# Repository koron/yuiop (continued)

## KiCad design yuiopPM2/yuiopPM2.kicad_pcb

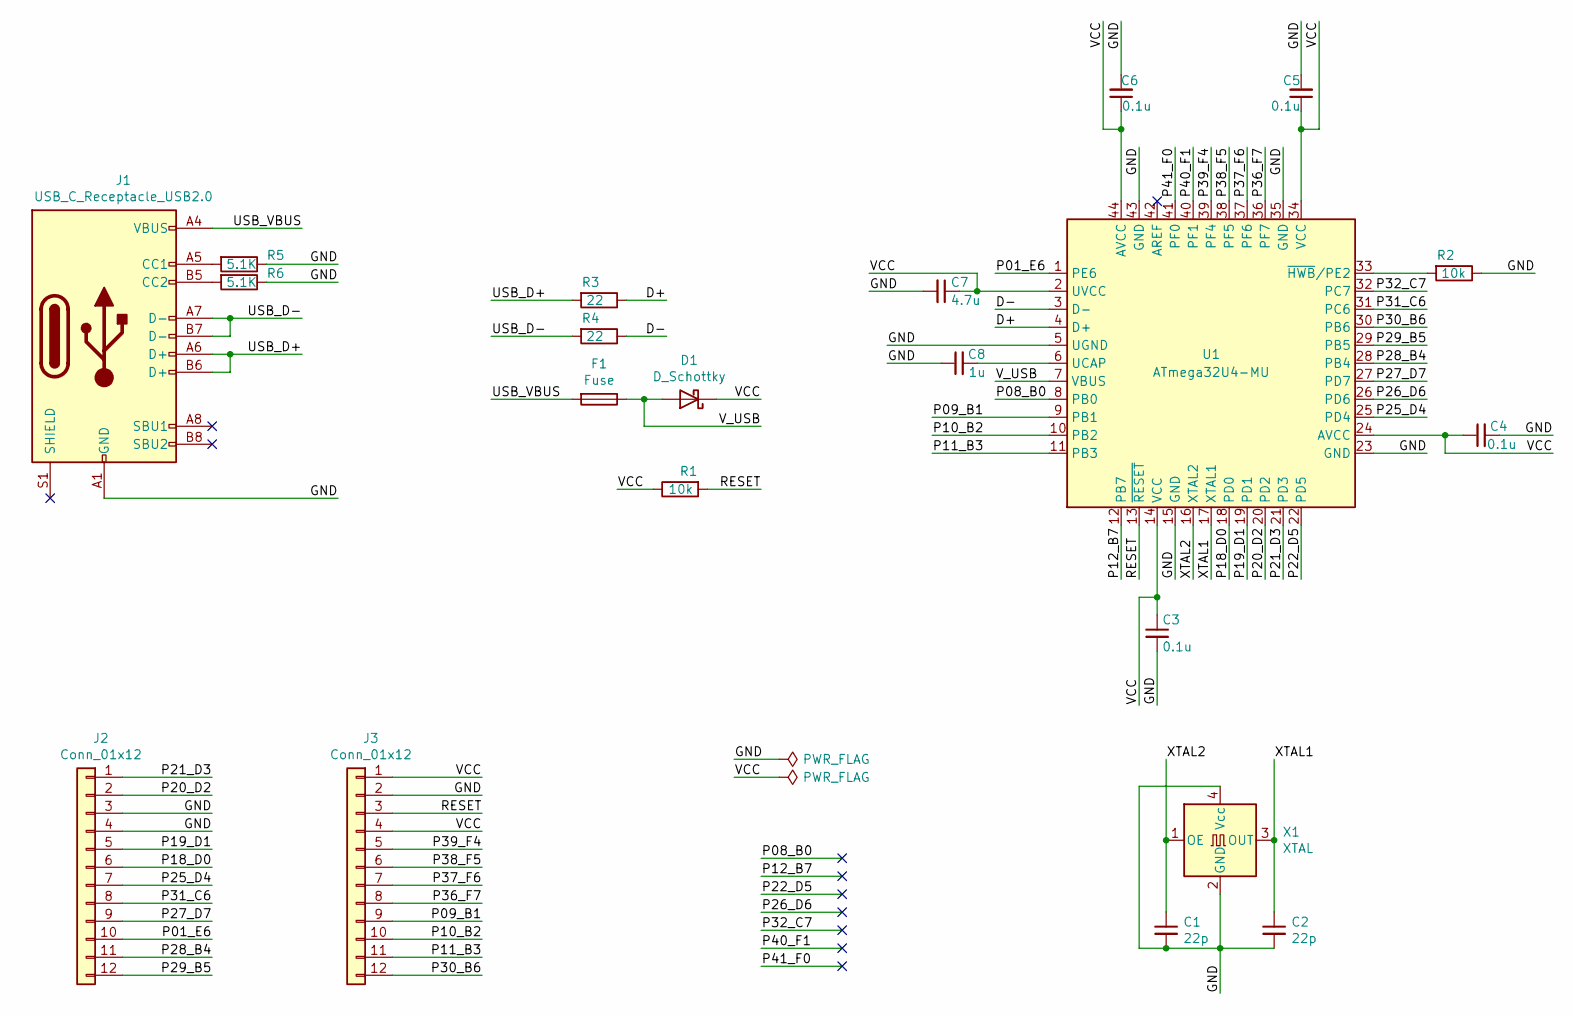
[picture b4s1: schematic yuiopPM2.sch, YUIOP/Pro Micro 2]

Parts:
C1, C2: 22p; C_0603_1608Metric
C3, C4, C5, C6: 0.1u; C_0603_1608Metric
C7: 4.7u; C_0603_1608Metric
C8: 1u; C_0603_1608Metric
D1: D_Schottky; D_SOD-123
F1: Fuse; Fuse_1206_3216Metric
J1: USB_C_Receptacle_USB2.0; USB_C_Receptacle_XKB_U262-16XN-4BVC11
J2, J3: Conn_01x12; SpringPinHeader-01x12
R1, R2: 10k; R_0603_1608Metric
R3, R4: 22; R_0603_1608Metric
R5, R6: 5.1K; R_0603_1608Metric
U1: ATmega32U4-MU; TQFP-44_10x10mm_P0.8mm
X1: XTAL; Oscillator_SMD_SeikoEpson_SG8002CE-4Pin_3.2x2.5mm

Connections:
/D+: R3.1, U1.4 (D+)
/D-: R4.1, U1.3 (D-)
/GND: C1.2, C2.2, C3.2, C4.2, C5.2, C6.2, C7.2, C8.1, J1.A1 (GND), J1.A12 (GND), J1.B1 (GND), J1.B12 (GND), J2.3, J2.4, J3.2, R2.1, R5.1, R6.1, U1.5 (UGND), U1.15 (GND), U1.23 (GND), U1.35 (GND), U1.43 (GND), X1.2 (GND), X1.4 (Vcc)
/P01_E6: J2.10, U1.1 (PE6)
/P08_B0: U1.8 (PB0)
/P09_B1: J3.9, U1.9 (PB1)
/P10_B2: J3.10, U1.10 (PB2)
/P11_B3: J3.11, U1.11 (PB3)
/P12_B7: U1.12 (PB7)
/P18_D0: J2.6, U1.18 (PD0)
/P19_D1: J2.5, U1.19 (PD1)
/P20_D2: J2.2, U1.20 (PD2)
/P21_D3: J2.1, U1.21 (PD3)
/P22_D5: U1.22 (PD5)
/P25_D4: J2.7, U1.25 (PD4)
/P26_D6: U1.26 (PD6)
/P27_D7: J2.9, U1.27 (PD7)
/P28_B4: J2.11, U1.28 (PB4)
/P29_B5: J2.12, U1.29 (PB5)
/P30_B6: J3.12, U1.30 (PB6)
/P31_C6: J2.8, U1.31 (PC6)
/P32_C7: U1.32 (PC7)
/P36_F7: J3.8, U1.36 (PF7)
/P37_F6: J3.7, U1.37 (PF6)
/P38_F5: J3.6, U1.38 (PF5)
/P39_F4: J3.5, U1.39 (PF4)
/P40_F1: U1.40 (PF1)
/P41_F0: U1.41 (PF0)
/RESET: J3.3, R1.2, U1.13 (~RESET)
/USB_D+: J1.A6 (D+), J1.B6 (D+), R3.2
/USB_D-: J1.A7 (D-), J1.B7 (D-), R4.2
/USB_VBUS: F1.2, J1.A4 (VBUS), J1.A9 (VBUS), J1.B4 (VBUS), J1.B9 (VBUS)
/VCC: C3.1, C4.1, C5.1, C6.1, C7.1, D1.1 (K), J3.1, J3.4, R1.1, U1.2 (UVCC), U1.14 (VCC), U1.24 (AVCC), U1.34 (VCC), U1.44 (AVCC)
/V_USB: D1.2 (A), F1.1, U1.7 (VBUS)
/XTAL1: C2.1, U1.17 (XTAL1), X1.3 (OUT)
/XTAL2: C1.1, U1.16 (XTAL2), X1.1 (OE)
unnamed: C8.2, U1.6 (UCAP)
unnamed: J1.A5 (CC1), R5.2
unnamed: J1.B5 (CC2), R6.2
unnamed: R2.2, U1.33 (~HWB~/PE2)

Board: 2 copper layers, 21 parts (0 on the bottom side), 33 nets, no tracks yet.

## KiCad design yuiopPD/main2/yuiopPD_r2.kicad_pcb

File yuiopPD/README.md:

# YUIOP/PD

"PD" means "Pointing Device".  A track ball and 6 buttons pointing device
project.

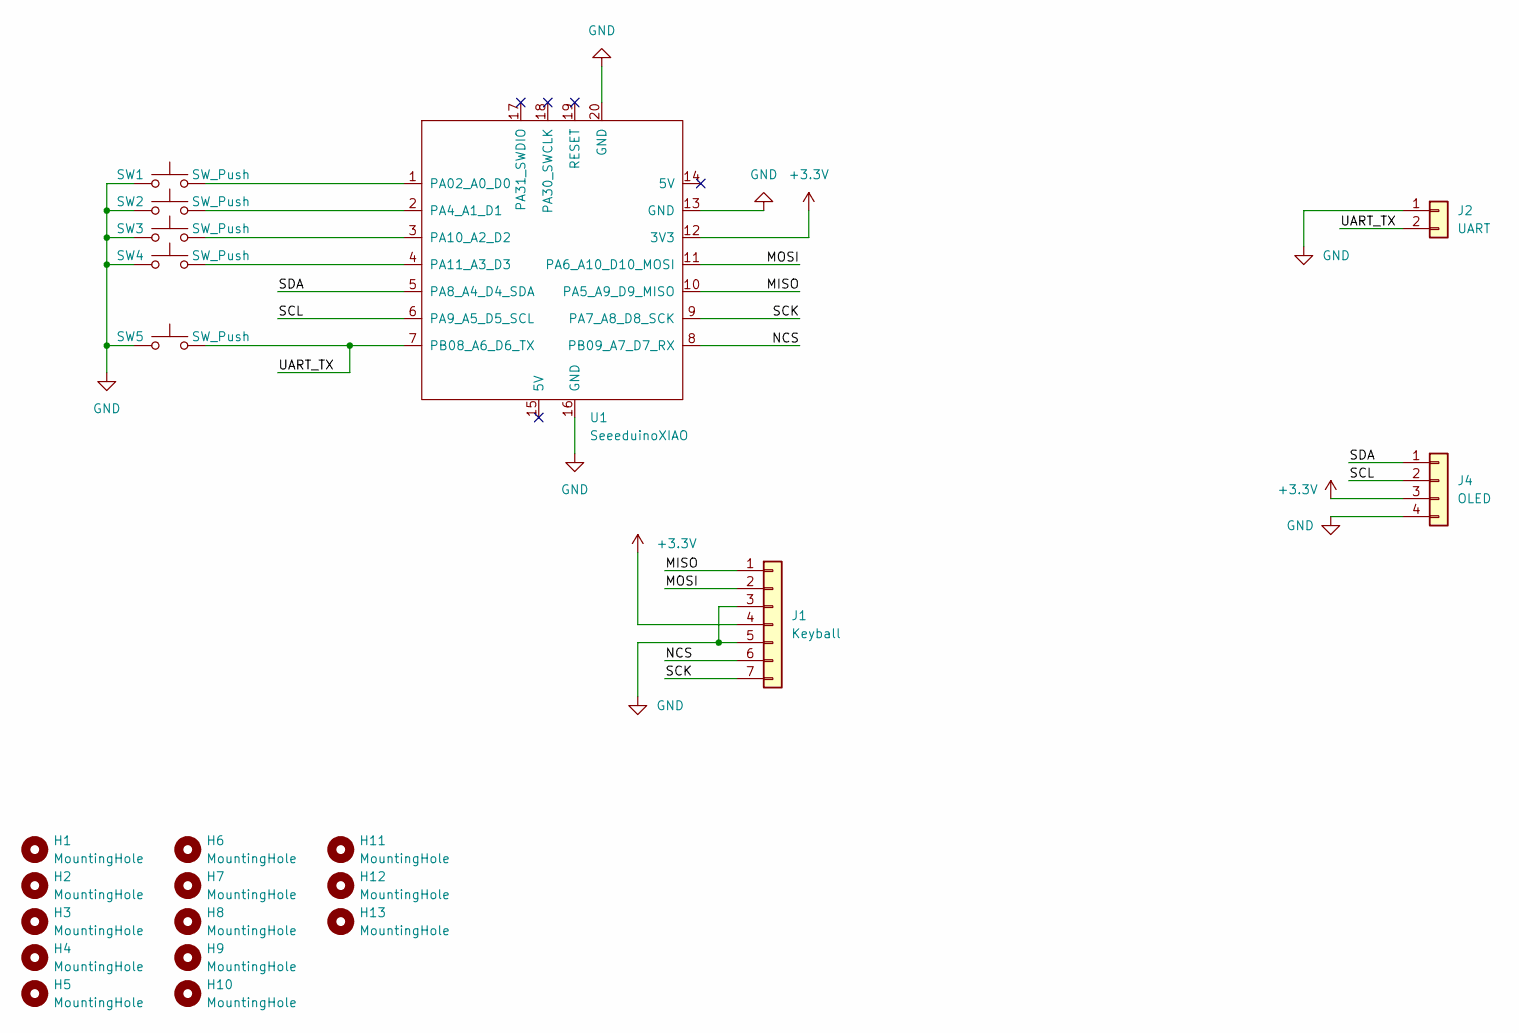
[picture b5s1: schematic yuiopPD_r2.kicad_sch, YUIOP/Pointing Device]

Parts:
H1, H2, H3, H4, H5, H6, H7, H8, H9, H10, H11, H12, H13: MountingHole; MountingHole_2.1mm
J1: Keyball; KeyballSensor_on_PCB
J2: UART; PinHeader_1x02_P2.54mm_Vertical
J4: OLED; OLED_128x32
SW1, SW2, SW3, SW4, SW5: SW_Push; SW_PUSH-12mm_v2
U1: SeeeduinoXIAO; Seeeduino XIAO TH r2

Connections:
+3V3: J1.4, J4.3, U1.12 (3V3)
/MISO: J1.1, U1.10 (PA5_A9_D9_MISO)
/MOSI: J1.2, U1.11 (PA6_A10_D10_MOSI)
/NCS: J1.6, U1.8 (PB09_A7_D7_RX)
/SCK: J1.7, U1.9 (PA7_A8_D8_SCK)
/SCL: J4.2, U1.6 (PA9_A5_D5_SCL)
/SDA: J4.1, U1.5 (PA8_A4_D4_SDA)
/UART_TX: J2.2, SW5.2, U1.7 (PB08_A6_D6_TX)
GND: J1.3, J1.5, J2.1, J4.4, SW1.1, SW2.1, SW3.1, SW4.1, SW5.1, U1.13 (GND), U1.16 (GND), U1.20 (GND)
unnamed: SW1.2, U1.1 (PA02_A0_D0)
unnamed: SW2.2, U1.2 (PA4_A1_D1)
unnamed: SW3.2, U1.3 (PA10_A2_D2)
unnamed: SW4.2, U1.4 (PA11_A3_D3)

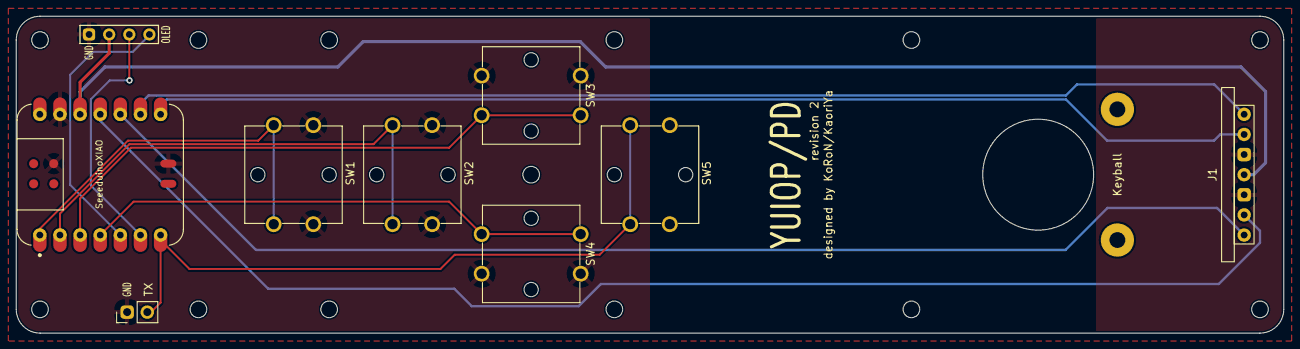
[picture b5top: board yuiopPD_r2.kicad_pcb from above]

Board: 2 copper layers, 160.0 x 40.0 mm, 22 parts (0 on the bottom side), 13 nets.

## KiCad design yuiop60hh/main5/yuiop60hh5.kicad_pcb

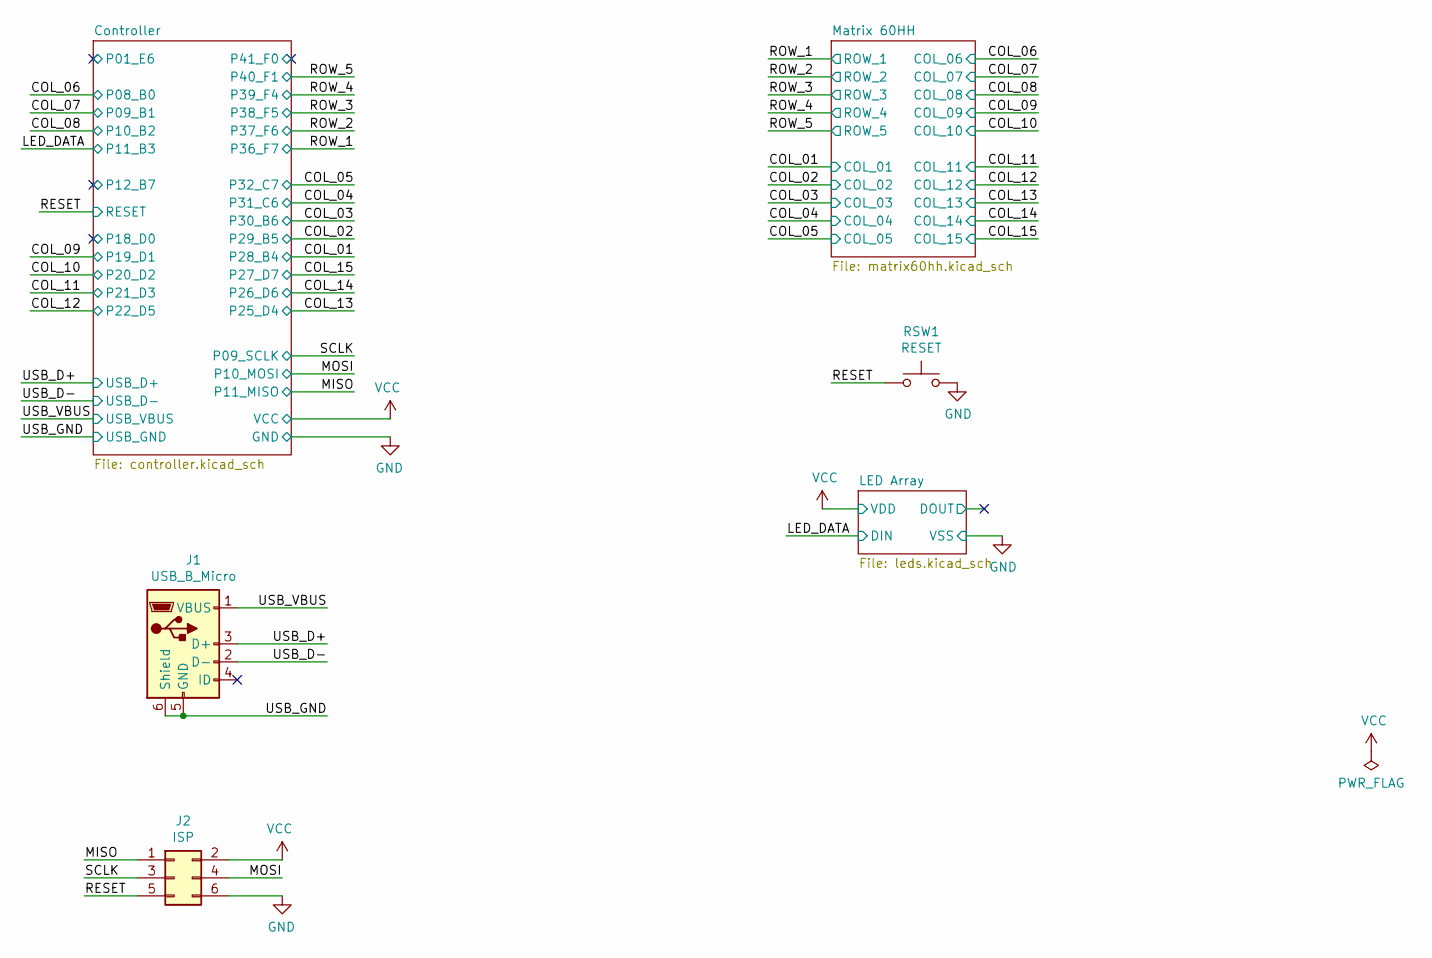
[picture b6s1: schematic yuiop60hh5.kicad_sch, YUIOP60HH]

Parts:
J1: USB_B_Micro; USB_Micro-B_Amphenol_10103594-0001LF_Horizontal
J2: ISP; PinHeader_2x03_P2.54mm_Vertical
RSW1: RESET; SW_Push_1P1T_NO_6x6mm_H9.5mm

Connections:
/COL_07: J2.3; also elsewhere on the board
/COL_08: J2.4; also elsewhere on the board
/LED_DATA: J2.1; also elsewhere on the board
/RESET: J2.5, RSW1.1; also elsewhere on the board
/USB_D+: J1.3 (D+); also elsewhere on the board
/USB_D-: J1.2 (D-); also elsewhere on the board
/USB_VBUS: J1.1 (VBUS); also elsewhere on the board
GND: J1.5 (GND), J1.6 (Shield), J2.6, RSW1.2; also elsewhere on the board
VCC: J2.2; also elsewhere on the board

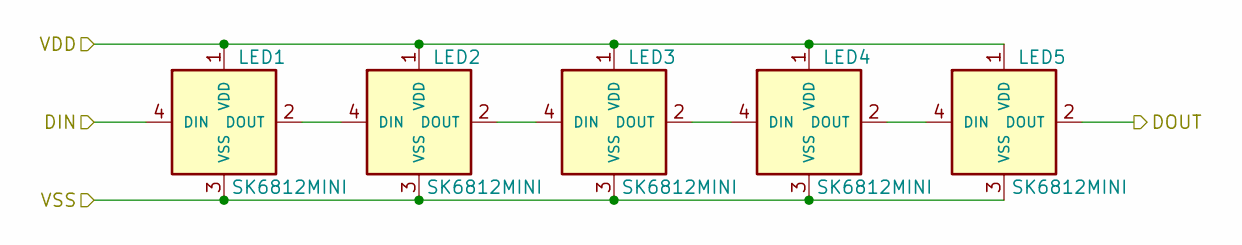
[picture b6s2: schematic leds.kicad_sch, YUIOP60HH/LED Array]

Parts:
LED1, LED2, LED3, LED4, LED5: SK6812MINI; SK6812MINI-E_B

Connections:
/LED Array/DOUT: LED5.2 (DOUT)
/LED_DATA: LED1.4 (DIN); also elsewhere on the board
GND: LED1.3 (VSS), LED2.3 (VSS), LED3.3 (VSS), LED4.3 (VSS), LED5.3 (VSS); also elsewhere on the board
unnamed: LED1.2 (DOUT), LED2.4 (DIN)
unnamed: LED2.2 (DOUT), LED3.4 (DIN)
unnamed: LED3.2 (DOUT), LED4.4 (DIN)
unnamed: LED4.2 (DOUT), LED5.4 (DIN)
VCC: LED1.1 (VDD), LED2.1 (VDD), LED3.1 (VDD), LED4.1 (VDD), LED5.1 (VDD); also elsewhere on the board

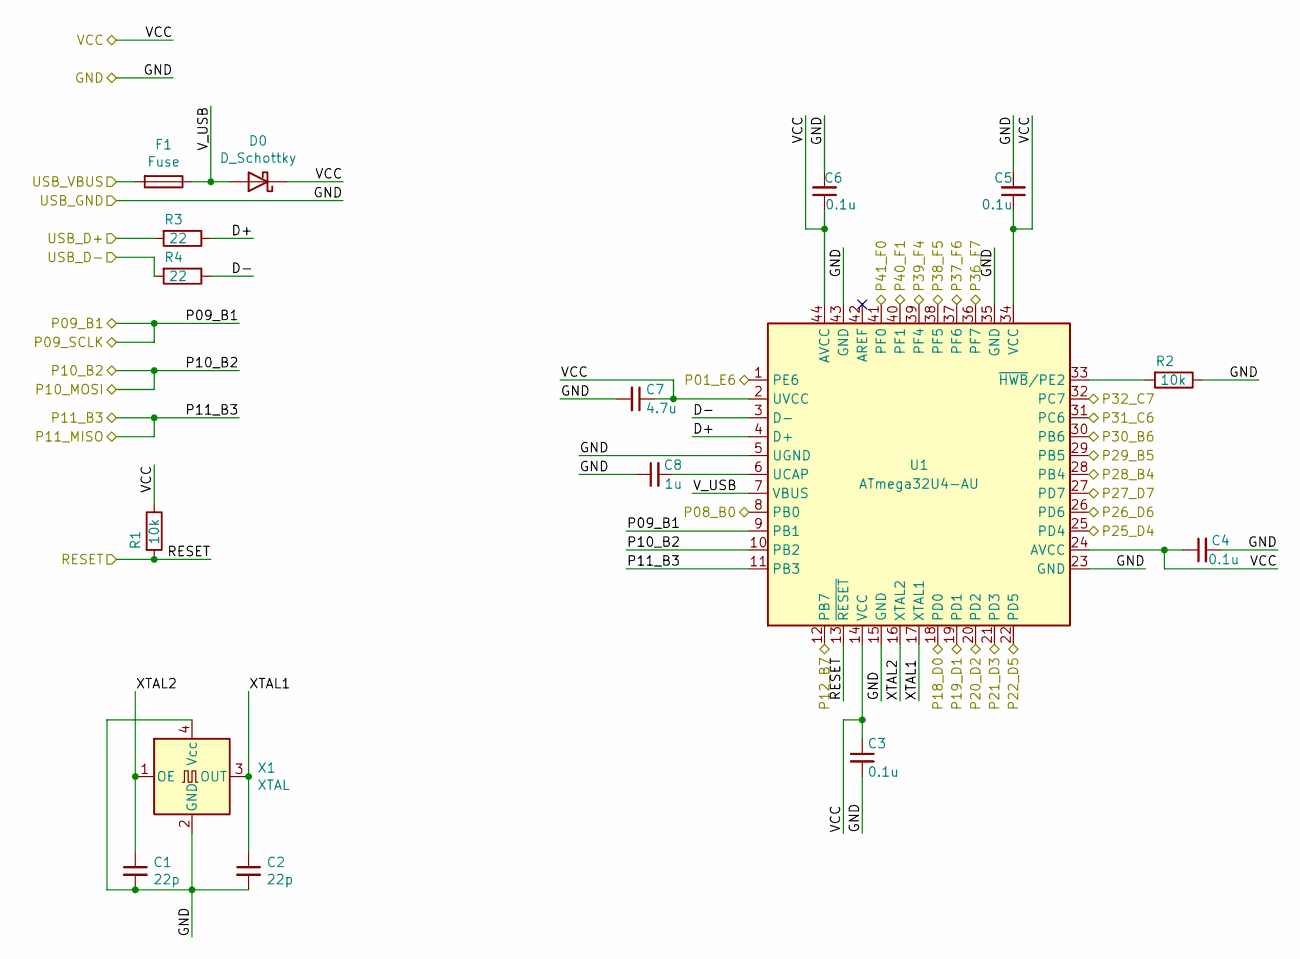
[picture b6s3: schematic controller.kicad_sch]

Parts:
C1, C2: 22p; C_0603_1608Metric_Pad1.08x0.95mm_HandSolder
C3, C4, C5, C6: 0.1u; C_0603_1608Metric_Pad1.08x0.95mm_HandSolder
C7: 4.7u; C_0603_1608Metric_Pad1.08x0.95mm_HandSolder
C8: 1u; C_0603_1608Metric_Pad1.08x0.95mm_HandSolder
D0: D_Schottky; D_SOD-123
F1: Fuse; Fuse_1206_3216Metric_Pad1.42x1.75mm_HandSolder
R1, R2: 10k; R_0603_1608Metric_Pad0.98x0.95mm_HandSolder
R3, R4: 22; R_0603_1608Metric_Pad0.98x0.95mm_HandSolder
U1: ATmega32U4-AU; TQFP-44_10x10mm_P0.8mm
X1: XTAL; Oscillator_SMD_SeikoEpson_SG8002CE-4Pin_3.2x2.5mm

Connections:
/COL_01: U1.28 (PB4); also elsewhere on the board
/COL_02: U1.29 (PB5); also elsewhere on the board
/COL_03: U1.30 (PB6); also elsewhere on the board
/COL_04: U1.31 (PC6); also elsewhere on the board
/COL_05: U1.32 (PC7); also elsewhere on the board
/COL_06: U1.8 (PB0); also elsewhere on the board
/COL_07: U1.9 (PB1); also elsewhere on the board
/COL_08: U1.10 (PB2); also elsewhere on the board
/COL_09: U1.19 (PD1); also elsewhere on the board
/COL_10: U1.20 (PD2); also elsewhere on the board
/COL_11: U1.21 (PD3); also elsewhere on the board
/COL_12: U1.22 (PD5); also elsewhere on the board
/COL_13: U1.25 (PD4); also elsewhere on the board
/COL_14: U1.26 (PD6); also elsewhere on the board
/COL_15: U1.27 (PD7); also elsewhere on the board
/Controller/D+: R3.1, U1.4 (D+)
/Controller/D-: R4.1, U1.3 (D-)
/Controller/P01_E6: U1.1 (PE6)
/Controller/P12_B7: U1.12 (PB7)
/Controller/P18_D0: U1.18 (PD0)
/Controller/P41_F0: U1.41 (PF0)
/Controller/V_USB: D0.2 (A), F1.1, U1.7 (VBUS)
/Controller/XTAL1: C2.1, U1.17 (XTAL1), X1.3 (OUT)
/Controller/XTAL2: C1.1, U1.16 (XTAL2), X1.1 (OE)
/LED_DATA: U1.11 (PB3); also elsewhere on the board
/RESET: R1.2, U1.13 (~RESET); also elsewhere on the board
/ROW_1: U1.36 (PF7); also elsewhere on the board
/ROW_2: U1.37 (PF6); also elsewhere on the board
/ROW_3: U1.38 (PF5); also elsewhere on the board
/ROW_4: U1.39 (PF4); also elsewhere on the board
/ROW_5: U1.40 (PF1); also elsewhere on the board
/USB_D+: R3.2; also elsewhere on the board
/USB_D-: R4.2; also elsewhere on the board
/USB_VBUS: F1.2; also elsewhere on the board
GND: C1.2, C2.2, C3.2, C4.2, C5.2, C6.2, C7.2, C8.1, R2.1, U1.5 (UGND), U1.15 (GND), U1.23 (GND), U1.35 (GND), U1.43 (GND), X1.2 (GND), X1.4 (Vcc); also elsewhere on the board
unnamed: C8.2, U1.6 (UCAP)
unnamed: R2.2, U1.33 (~HWB/PE2)
VCC: C3.1, C4.1, C5.1, C6.1, C7.1, D0.1 (K), R1.1, U1.2 (UVCC), U1.14 (VCC), U1.24 (AVCC), U1.34 (VCC), U1.44 (AVCC); also elsewhere on the board

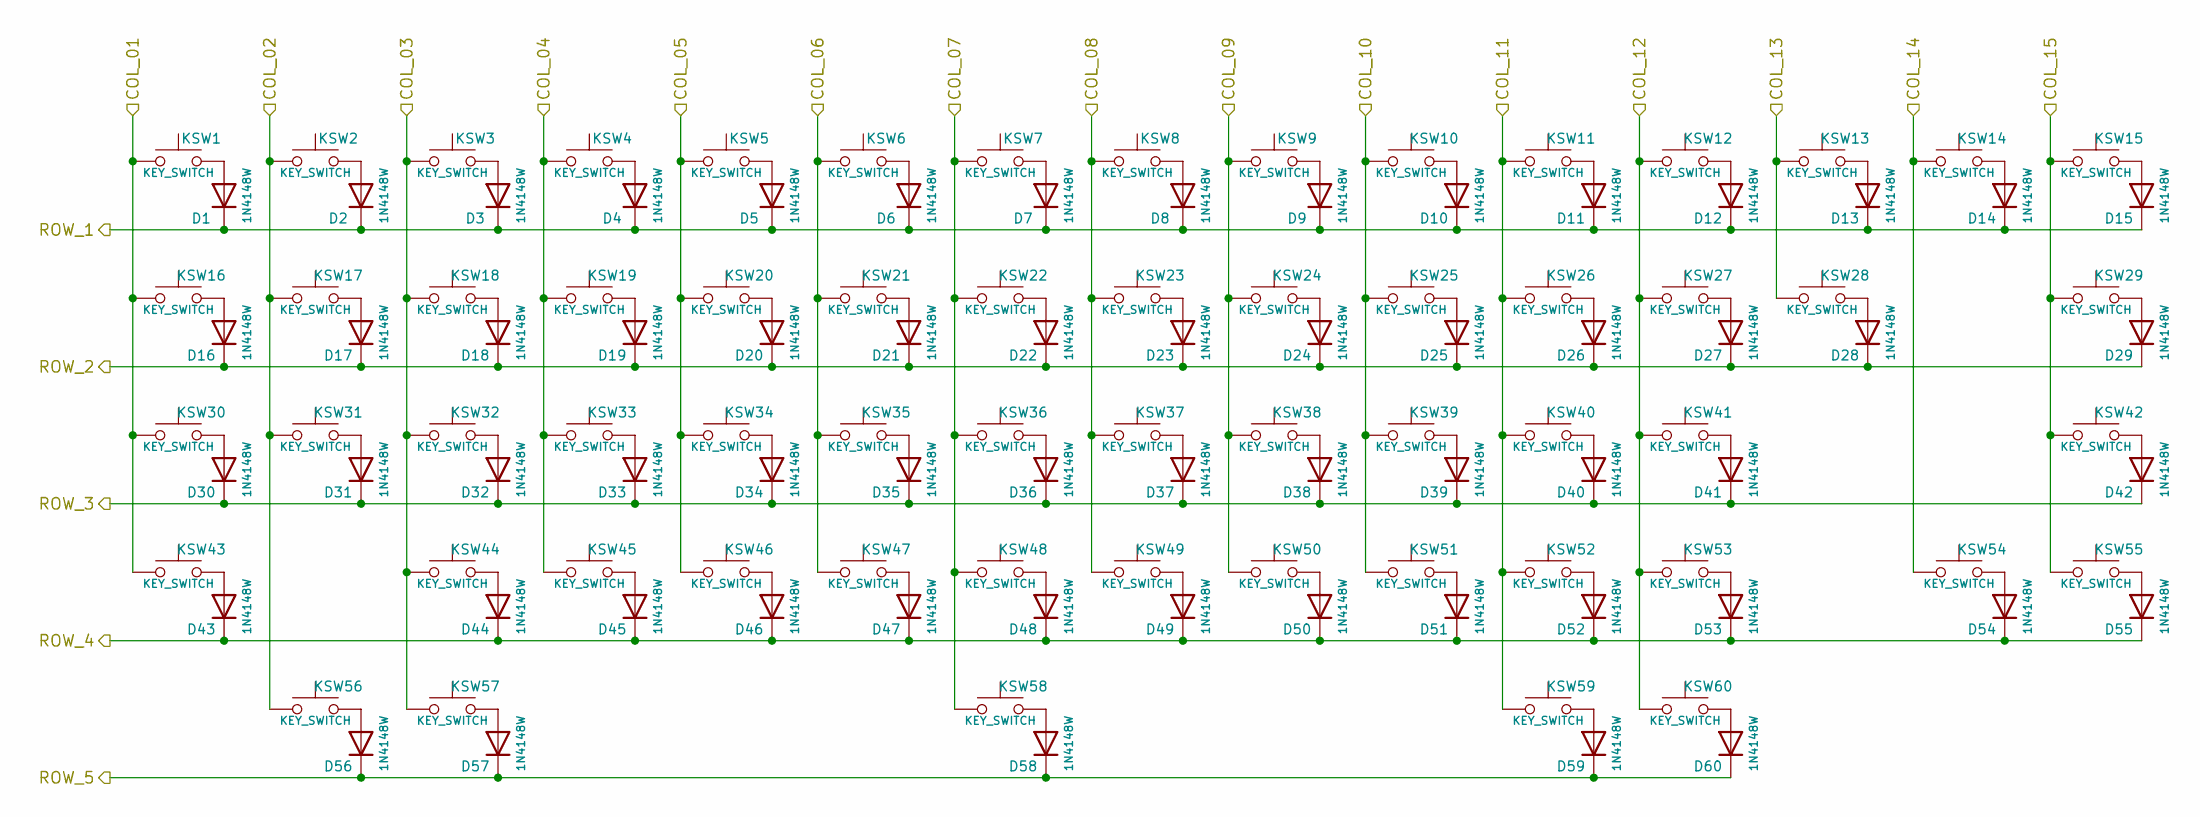
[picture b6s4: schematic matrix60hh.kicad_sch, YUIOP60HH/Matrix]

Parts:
D1, D2, D3, D4, D5, D6, D7, D8, D9, D10, D11, D12, D13, D14, D15, D16, D17, D18, D19, D20, D21, D22, D23, D24, D25, D26, D27, D28, D29, D30, D31, D32, D33, D34, D35, D36, D37, D38, D39, D40, D41, D42, D43, D44, D45, D46, D47, D48, D49, D50, D51, D52, D53, D54, D55, D56, D57, D58, D59, D60: 1N4148W; D_SOD-123
KSW1, KSW2, KSW3, KSW4, KSW5, KSW6, KSW7, KSW8, KSW9, KSW10, KSW11, KSW12, KSW13, KSW14, KSW15, KSW16, KSW17, KSW18, KSW19, KSW20, KSW21, KSW22, KSW23, KSW24, KSW25, KSW26, KSW27, KSW28, KSW29, KSW30, KSW31, KSW32, KSW33, KSW34, KSW35, KSW36, KSW37, KSW38, KSW39, KSW40, KSW41, KSW42, KSW43, KSW44, KSW45, KSW46, KSW47, KSW48, KSW49, KSW50, KSW51, KSW52, KSW53, KSW54, KSW55, KSW56, KSW57, KSW58, KSW59, KSW60: KEY_SWITCH; Cherry_MX_Hotswap_1.0u

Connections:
/COL_01: KSW1.1, KSW16.1, KSW30.1, KSW43.1; also elsewhere on the board
/COL_02: KSW2.1, KSW17.1, KSW31.1, KSW56.1; also elsewhere on the board
/COL_03: KSW3.1, KSW18.1, KSW32.1, KSW44.1, KSW57.1; also elsewhere on the board
/COL_04: KSW4.1, KSW19.1, KSW33.1, KSW45.1; also elsewhere on the board
/COL_05: KSW5.1, KSW20.1, KSW34.1, KSW46.1; also elsewhere on the board
/COL_06: KSW6.1, KSW21.1, KSW35.1, KSW47.1; also elsewhere on the board
/COL_07: KSW7.1, KSW22.1, KSW36.1, KSW48.1, KSW58.1; also elsewhere on the board
/COL_08: KSW8.1, KSW23.1, KSW37.1, KSW49.1; also elsewhere on the board
/COL_09: KSW9.1, KSW24.1, KSW38.1, KSW50.1; also elsewhere on the board
/COL_10: KSW10.1, KSW25.1, KSW39.1, KSW51.1; also elsewhere on the board
/COL_11: KSW11.1, KSW26.1, KSW40.1, KSW52.1, KSW59.1; also elsewhere on the board
/COL_12: KSW12.1, KSW27.1, KSW41.1, KSW53.1, KSW60.1; also elsewhere on the board
/COL_13: KSW13.1, KSW28.1; also elsewhere on the board
/COL_14: KSW14.1, KSW54.1; also elsewhere on the board
/COL_15: KSW15.1, KSW29.1, KSW42.1, KSW55.1; also elsewhere on the board
/ROW_1: D1.1 (K), D2.1 (K), D3.1 (K), D4.1 (K), D5.1 (K), D6.1 (K), D7.1 (K), D8.1 (K), D9.1 (K), D10.1 (K), D11.1 (K), D12.1 (K), D13.1 (K), D14.1 (K), D15.1 (K); also elsewhere on the board
/ROW_2: D16.1 (K), D17.1 (K), D18.1 (K), D19.1 (K), D20.1 (K), D21.1 (K), D22.1 (K), D23.1 (K), D24.1 (K), D25.1 (K), D26.1 (K), D27.1 (K), D28.1 (K), D29.1 (K); also elsewhere on the board
/ROW_3: D30.1 (K), D31.1 (K), D32.1 (K), D33.1 (K), D34.1 (K), D35.1 (K), D36.1 (K), D37.1 (K), D38.1 (K), D39.1 (K), D40.1 (K), D41.1 (K), D42.1 (K); also elsewhere on the board
/ROW_4: D43.1 (K), D44.1 (K), D45.1 (K), D46.1 (K), D47.1 (K), D48.1 (K), D49.1 (K), D50.1 (K), D51.1 (K), D52.1 (K), D53.1 (K), D54.1 (K), D55.1 (K); also elsewhere on the board
/ROW_5: D56.1 (K), D57.1 (K), D58.1 (K), D59.1 (K), D60.1 (K); also elsewhere on the board
unnamed: D1.2 (A), KSW1.2
unnamed: D2.2 (A), KSW2.2
unnamed: D3.2 (A), KSW3.2
unnamed: D4.2 (A), KSW4.2
unnamed: D5.2 (A), KSW5.2
unnamed: D6.2 (A), KSW6.2
unnamed: D7.2 (A), KSW7.2
unnamed: D8.2 (A), KSW8.2
unnamed: D9.2 (A), KSW9.2
unnamed: D10.2 (A), KSW10.2
unnamed: D11.2 (A), KSW11.2
unnamed: D12.2 (A), KSW12.2
unnamed: D13.2 (A), KSW13.2
unnamed: D14.2 (A), KSW14.2
unnamed: D15.2 (A), KSW15.2
unnamed: D16.2 (A), KSW16.2
unnamed: D17.2 (A), KSW17.2
unnamed: D18.2 (A), KSW18.2
unnamed: D19.2 (A), KSW19.2
unnamed: D20.2 (A), KSW20.2
unnamed: D21.2 (A), KSW21.2
unnamed: D22.2 (A), KSW22.2
unnamed: D23.2 (A), KSW23.2
unnamed: D24.2 (A), KSW24.2
unnamed: D25.2 (A), KSW25.2
unnamed: D26.2 (A), KSW26.2
unnamed: D27.2 (A), KSW27.2
unnamed: D28.2 (A), KSW28.2
unnamed: D29.2 (A), KSW29.2
unnamed: D30.2 (A), KSW30.2
unnamed: D31.2 (A), KSW31.2
unnamed: D32.2 (A), KSW32.2
unnamed: D33.2 (A), KSW33.2
unnamed: D34.2 (A), KSW34.2
unnamed: D35.2 (A), KSW35.2
unnamed: D36.2 (A), KSW36.2
unnamed: D37.2 (A), KSW37.2
unnamed: D38.2 (A), KSW38.2
unnamed: D39.2 (A), KSW39.2
unnamed: D40.2 (A), KSW40.2
unnamed: D41.2 (A), KSW41.2
unnamed: D42.2 (A), KSW42.2
unnamed: D43.2 (A), KSW43.2
unnamed: D44.2 (A), KSW44.2
unnamed: D45.2 (A), KSW45.2
unnamed: D46.2 (A), KSW46.2
unnamed: D47.2 (A), KSW47.2
unnamed: D48.2 (A), KSW48.2
unnamed: D49.2 (A), KSW49.2
unnamed: D50.2 (A), KSW50.2
unnamed: D51.2 (A), KSW51.2
unnamed: D52.2 (A), KSW52.2
unnamed: D53.2 (A), KSW53.2
unnamed: D54.2 (A), KSW54.2
unnamed: D55.2 (A), KSW55.2
unnamed: D56.2 (A), KSW56.2
unnamed: D57.2 (A), KSW57.2
unnamed: D58.2 (A), KSW58.2
unnamed: D59.2 (A), KSW59.2
unnamed: D60.2 (A), KSW60.2

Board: 2 copper layers, 159 parts (19 on the bottom side), 98 nets, no tracks yet.

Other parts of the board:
HOLE1, HOLE2, HOLE4: Hole_5x2.3_6; Hole_5x2.5_7
HOLE3: Hole_2.3; Hole_2.2
HOLE5, HOLE6: Hole_7x2.5; Hole_7x2.5_10x5
HOLE7, HOLE8, HOLE9, HOLE10, HOLE11, HOLE12: Hole_2.2_4
STB1, STB3: Cherry_MX_Stabilizer
STB2: Cherry_MX_Stabilizer_6.0u

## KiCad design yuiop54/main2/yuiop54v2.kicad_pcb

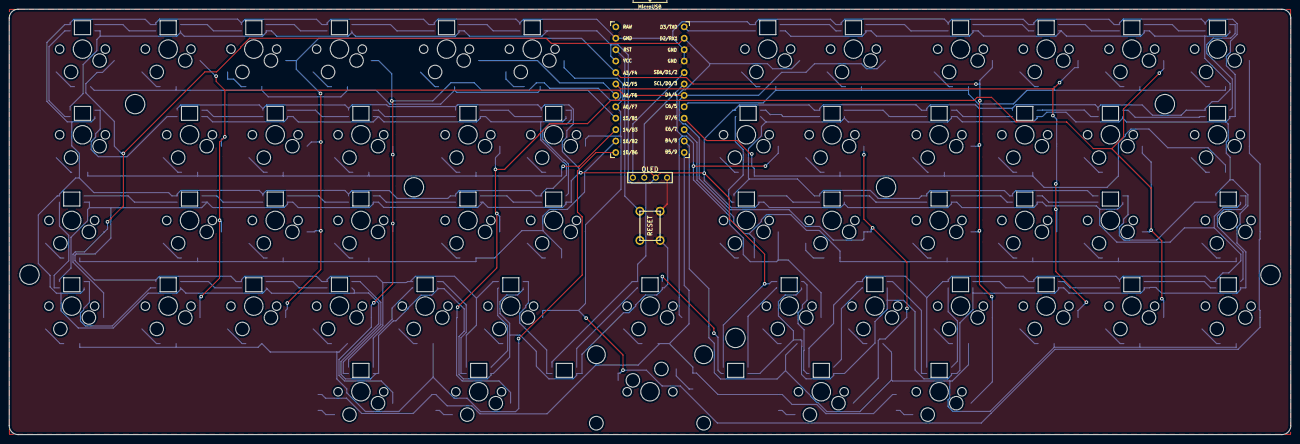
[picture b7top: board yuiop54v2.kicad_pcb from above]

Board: 2 copper layers, 285.0 x 94.6 mm, 174 parts (0 on the bottom side), 129 nets.

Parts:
D1, D2, D3, D4, D5, D6, D7, D8, D9, D10, D11, D12, D13, D14, D15, D16, D17, D18, D19, D20, D21, D22, D23, D24, D25, D26, D27, D28, D29, D30, D31, D32, D33, D34, D35, D36, D37, D38, D39, D40, D41, D42, D43, D44, D45, D46, D47, D48, D49, D50, D51, D52, D53, D54: D; D3_SMD_v2_B
HOLE1, HOLE2, HOLE3, HOLE4, HOLE5, HOLE6, HOLE7: Val**; Hole_4.3
LED1, LED2, LED3, LED4, LED5, LED6, LED7, LED8, LED9, LED10, LED11, LED12, LED13, LED14, LED15, LED16, LED17, LED18, LED19, LED20, LED21, LED22, LED23, LED24, LED25, LED26, LED27, LED28, LED29, LED30, LED31, LED32, LED33, LED34, LED35, LED36, LED37, LED38, LED39, LED40, LED41, LED42, LED43, LED44, LED45, LED46, LED47, LED48, LED49, LED50, LED51, LED52, LED53, LED54, LED55: YS-SK6812MINI-E; SK6812MINI-E_B
OL1: OLED; OLED_128x32
STB1: Cherry_MX_Stabilizer
SW1, SW2, SW3, SW4, SW5, SW6, SW7, SW8, SW9, SW10, SW11, SW12, SW14, SW15, SW16, SW17, SW18, SW19, SW20, SW21, SW22, SW23, SW26, SW27, SW28, SW29, SW30, SW31, SW32, SW33, SW34, SW35, SW38, SW39, SW40, SW41, SW42, SW43, SW44, SW45, SW46, SW47: SW_PUSH; Cherry_MX_Hotswap_1u
SW13, SW24, SW50, SW54: SW_PUSH; Cherry_MX_Hotswap_1.5u
SW25, SW36: SW_PUSH; Cherry_MX_Hotswap_1.75u
SW37, SW48, SW49, SW51, SW53: SW_PUSH; Cherry_MX_Hotswap_1.25u
SW52: SW_PUSH; Cherry_MX_Hotswap_2.75u
SW_RST1: SW_PUSH; ResetSW_4_1side
U1: ProMicro; ProMicro_v3

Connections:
/COL1: SW1.1, SW7.1, SW13.1, SW19.1, SW25.1, SW31.1, SW37.1, SW43.1, SW49.1, U1.2
/COL2: SW2.1, SW8.1, SW14.1, SW20.1, SW26.1, SW32.1, SW38.1, SW44.1, SW53.1, U1.7
/COL3: SW3.1, SW9.1, SW15.1, SW21.1, SW27.1, SW33.1, SW39.1, SW45.1, SW54.1, U1.20
/COL4: SW4.1, SW10.1, SW16.1, SW22.1, SW28.1, SW34.1, SW40.1, SW46.1, SW50.1, U1.19
/COL5: SW5.1, SW11.1, SW17.1, SW23.1, SW29.1, SW35.1, SW41.1, SW47.1, SW51.1, U1.18
/COL6: SW6.1, SW12.1, SW18.1, SW24.1, SW30.1, SW36.1, SW42.1, SW48.1, SW52.1, U1.17
/LED: LED1.4, U1.1
/ROW1: D7.1, D8.1, D9.1, D10.1, D11.1, D12.1, U1.8
/ROW2: D1.1, D2.1, D3.1, D4.1, D5.1, D6.1, U1.16
/ROW3: D19.1, D20.1, D21.1, D22.1, D23.1, D24.1, U1.9
/ROW4: D13.1, D14.1, D15.1, D16.1, D17.1, D18.1, U1.15
/ROW5: D31.1, D32.1, D33.1, D34.1, D35.1, D36.1, U1.10
/ROW6: D25.1, D26.1, D27.1, D28.1, D29.1, D30.1, U1.14
/ROW7: D43.1, D44.1, D45.1, D46.1, D47.1, D48.1, U1.11
/ROW8: D37.1, D38.1, D39.1, D40.1, D41.1, D42.1, U1.13
/ROW9: D49.1, D50.1, D51.1, D52.1, D53.1, D54.1, U1.12
/RST: SW_RST1.1, U1.22
/SDA: OL1.1, U1.5
/SDL: OL1.2, U1.6
GND: LED1.3, LED2.3, LED3.3, LED4.3, LED5.3, LED6.3, LED7.3, LED8.3, LED9.3, LED10.3, LED11.3, LED12.3, LED13.3, LED14.3, LED15.3, LED16.3, LED17.3, LED18.3, LED19.3, LED20.3, LED21.3, LED22.3, LED23.3, LED24.3, LED25.3, LED26.3, LED27.3, LED28.3, LED29.3, LED30.3, LED31.3, LED32.3, LED33.3, LED34.3, LED35.3, LED36.3, LED37.3, LED38.3, LED39.3, LED40.3, LED41.3, LED42.3, LED43.3, LED44.3, LED45.3, LED46.3, LED47.3, LED48.3, LED49.3, LED50.3, LED51.3, LED52.3, LED53.3, LED54.3, LED55.3, OL1.4, SW_RST1.2, U1.3, U1.4, U1.23
unnamed: D1.2, SW1.2
unnamed: D2.2, SW2.2
unnamed: D3.2, SW3.2
unnamed: D4.2, SW4.2
unnamed: D5.2, SW5.2
unnamed: D6.2, SW6.2
unnamed: D7.2, SW7.2
unnamed: D8.2, SW8.2
unnamed: D9.2, SW9.2
unnamed: D10.2, SW10.2
unnamed: D11.2, SW11.2
unnamed: D12.2, SW12.2
unnamed: D13.2, SW13.2
unnamed: D14.2, SW14.2
unnamed: D15.2, SW15.2
unnamed: D16.2, SW16.2
unnamed: D17.2, SW17.2
unnamed: D18.2, SW18.2
unnamed: D19.2, SW19.2
unnamed: D20.2, SW20.2
unnamed: D21.2, SW21.2
unnamed: D22.2, SW22.2
unnamed: D23.2, SW23.2
unnamed: D24.2, SW24.2
unnamed: D25.2, SW25.2
unnamed: D26.2, SW26.2
unnamed: D27.2, SW27.2
unnamed: D28.2, SW28.2
unnamed: D29.2, SW29.2
unnamed: D30.2, SW30.2
unnamed: D31.2, SW31.2
unnamed: D32.2, SW32.2
unnamed: D33.2, SW33.2
unnamed: D34.2, SW34.2
unnamed: D35.2, SW35.2
unnamed: D36.2, SW36.2
unnamed: D37.2, SW37.2
unnamed: D38.2, SW38.2
unnamed: D39.2, SW39.2
unnamed: D40.2, SW40.2
unnamed: D41.2, SW41.2
unnamed: D42.2, SW42.2
unnamed: D43.2, SW43.2
unnamed: D44.2, SW44.2
unnamed: D45.2, SW45.2
unnamed: D46.2, SW46.2
unnamed: D47.2, SW47.2
unnamed: D48.2, SW48.2
unnamed: D49.2, SW49.2
unnamed: D50.2, SW50.2
unnamed: D51.2, SW51.2
unnamed: D52.2, SW52.2
unnamed: D53.2, SW53.2
unnamed: D54.2, SW54.2
unnamed: LED1.2, LED2.4
unnamed: LED2.2, LED3.4
unnamed: LED3.2, LED4.4
unnamed: LED4.2, LED5.4
unnamed: LED5.2, LED6.4
unnamed: LED6.2, LED7.4
unnamed: LED7.2, LED8.4
unnamed: LED8.2, LED9.4
unnamed: LED10.2, LED11.4
unnamed: LED9.2, LED10.4
unnamed: LED11.2, LED12.4
unnamed: LED12.2, LED13.4
unnamed: LED13.2, LED14.4
unnamed: LED14.2, LED15.4
unnamed: LED15.2, LED16.4
unnamed: LED16.2, LED17.4
unnamed: LED17.2, LED18.4
unnamed: LED18.2, LED19.4
unnamed: LED19.2, LED20.4
unnamed: LED20.2, LED21.4
unnamed: LED21.2, LED22.4
unnamed: LED22.2, LED23.4
unnamed: LED23.2, LED24.4
unnamed: LED24.2, LED25.4
unnamed: LED25.2, LED26.4
unnamed: LED26.2, LED27.4
unnamed: LED27.2, LED28.4
unnamed: LED28.2, LED29.4
unnamed: LED29.2, LED30.4
unnamed: LED30.2, LED31.4
unnamed: LED31.2, LED32.4
unnamed: LED32.2, LED33.4
unnamed: LED33.2, LED34.4
unnamed: LED34.2, LED35.4
unnamed: LED35.2, LED36.4
unnamed: LED36.2, LED37.4
unnamed: LED37.2, LED38.4
unnamed: LED38.2, LED39.4
unnamed: LED39.2, LED40.4
unnamed: LED40.2, LED41.4
unnamed: LED41.2, LED42.4
unnamed: LED42.2, LED43.4
unnamed: LED43.2, LED44.4
unnamed: LED44.2, LED45.4
unnamed: LED45.2, LED46.4
unnamed: LED46.2, LED47.4
unnamed: LED47.2, LED48.4
unnamed: LED48.2, LED49.4
unnamed: LED49.2, LED50.4
unnamed: LED50.2, LED51.4
unnamed: LED51.2, LED52.4
unnamed: LED52.2, LED53.4
unnamed: LED53.2, LED54.4
unnamed: LED54.2, LED55.4
VCC: LED1.1, LED2.1, LED3.1, LED4.1, LED5.1, LED6.1, LED7.1, LED8.1, LED9.1, LED10.1, LED11.1, LED12.1, LED13.1, LED14.1, LED15.1, LED16.1, LED17.1, LED18.1, LED19.1, LED20.1, LED21.1, LED22.1, LED23.1, LED24.1, LED25.1, LED26.1, LED27.1, LED28.1, LED29.1, LED30.1, LED31.1, LED32.1, LED33.1, LED34.1, LED35.1, LED36.1, LED37.1, LED38.1, LED39.1, LED40.1, LED41.1, LED42.1, LED43.1, LED44.1, LED45.1, LED46.1, LED47.1, LED48.1, LED49.1, LED50.1, LED51.1, LED52.1, LED53.1, LED54.1, LED55.1, OL1.3, U1.21

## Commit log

2021-01-10 initial commit (lib missing)
2021-01-10 add kbd library
    ref: https://github.com/foostan/kbd
2021-01-10 make references unique
2021-01-10 layouts
2021-01-11 YUIOP 54 layout
2021-01-11 separate dir of YUIOP27 project
2021-01-11 YUIOP54 project and schematic and footprints
2021-01-11 wired YUIOP55
2021-01-12 replace by auto routing version
2021-01-13 holes
2021-01-14 add GH60-compatible footprints
2021-01-14 add yuiop54v2 project and schematics
2021-01-16 update yuiop27
2021-01-16 add yuiop54v2
2021-01-16 remove unused pcb
2021-01-17 more footprints
2021-01-17 add PCBs variations of yuiop54v2
2021-01-17 yuiop54 layout trials
2021-01-19 add YUIOP variations
2021-01-19 design YUIOP47
2021-01-25 fix footprints of stabilizers
2021-01-26 yuiop47: swap LED's VCC/GND
2021-01-26 add yuiop64hh
2021-01-26 add yuiop60hh2
2021-01-26 yuiop60hh/2 auto wired
2021-02-11 key switch variations
2021-02-11 RPiPico symbol and footprint
2021-02-12 yuiop50d: rollout rev.1
2021-02-12 yuiop50d: gerber files for JLCPCB rev.1
2021-02-12 fix doc
2021-02-12 simple CherryMX switch footprint
2021-02-12 yuiop63hhs: rollout rev.1
2021-02-13 yuiop22rs: rollout rev.1
2021-03-03 design keyboard controller unit
2021-03-21 controller: fill footprints
2021-03-21 yuiopPM: new project
2021-03-29 MIT license
2021-04-09 misc fix
2021-04-10 yuiop60hh3: HHKB layout, 60% case compatible
2021-04-11 yuiop60hh3: finish top plate, generate gerbers
2021-04-12 yuiop60hh3: revision 2, start
2021-04-13 yuiop60hh3-rev2: reduce via
2021-04-13 rename files
2021-04-15 yuiopPM: biuld guide
2021-04-15 yuiopPM: fix diagrams
2021-04-15 yuiopPM: fix doc
2021-04-15 link to video to assemble
2021-04-16 yuiopPM: enlarge pin header's holes
2021-04-21 yuiop60hh3-r2: beta finish
2021-04-21 rename to yuiop60hh4 <- yuiop60hh3-r2
2021-04-21 rename to topplate
2021-04-21 yuiop60hh4: generate gerber files
2021-04-22 remove targets
2021-05-02 yuioppm: doc about soldering iron tip
2021-05-02 WS2812C-2020: add a symbol and footprints
2021-05-21 new keyboard yuiop31rs
2021-05-21 yuiop31rs: fix circuit, generate gerbers
2021-05-21 yuiop31rs: summary in README.md
2021-05-29 fix footprints after yuiop31rs production
2021-05-29 yuiop31rs rev.2, production
2021-05-30 Pro Micro (SMD) footprint
2021-05-30 fix legends
2021-05-30 fix: close court yard
2021-07-04 update stabilizer's footprints
2021-07-10 joystick schematic and footprint
2021-09-29 library for PGA2040
2021-09-30 yuiop60pi: layout footprints
2021-09-30 yuiop60pi: move LEDs
2021-10-01 yuiop60pi: wiring, design work
2021-10-01 yuiop60pi: draw top plate. move main board
2021-10-01 yuiop60pi: generate gerber files for JLCPCB
2021-10-02 yuiop60hh4: add metal (brass) top plate
2021-10-23 TW13-3-13 plates outline
2021-10-24 yuiop60pi rev. 1.2
2021-10-24 yuiop60pi: plot gerber files for rev 1.2
2021-10-25 add TW13-3-18 board schematics
2021-11-03 yuiop60s design files
2021-11-03 revision 3
2021-11-03 wired
2021-11-04 yuiop60pi/3: brush up
2021-11-20 yuiop60pi-r3: README
2021-11-20 add QR code
2021-11-21 yuiop60pi: plot gerber files for rev 3
2021-12-20 contacts order
2021-12-28 yuiop60pi-r3: build guide, skeleton
2021-12-28 fix, markup symbols
2021-12-28 add links for additional parts
2021-12-28 yuiop60pi: image of abstract structure
2021-12-28 snip
2021-12-28 fix format
2021-12-29 write build steps 1 and 2
2021-12-29 soldering docs
2021-12-29 finish build guide text
2022-01-22 ignore project local setting file
2022-02-04 consolidate yuiop60hh
2022-02-04 consolidate yuiop54 series
2022-02-04 YUIOP60HH rev.5: begin
2022-02-05 YUIOP60HH rev.5: finished
2022-02-05 YUIOP60HH: add firmwares
2022-02-05 how to write firmware
2022-02-11 rp2040 board introduced
2022-02-13 YUIOP2040: RP2040 base controller board
2022-02-13 yuiop2040: add gerbers
2022-02-19 yuiop60hh5: update firmware
2022-02-26 parts list
2022-03-04 yuiop2040: rev.2
2022-06-18 yuiop32dm: initial version
2022-06-18 yuiop32dm: rev.1 finish
2022-06-18 yuiop32dm: top plate
2022-06-18 yuiop32dm: output gerber files
2022-12-09 design YUIOP60HH5 new top plate
2022-12-10 yuiop60hh5: top plate r5
2023-01-08 add new project: yuiopPD
2023-01-09 yuiopPD: finish grand design
2023-01-09 yuiopPD: finish rev.1
2023-01-09 yuiopPD: move to main/ dir
2023-01-09 yuiopPD: output gerber files
2023-01-23 add drill file
2023-01-23 yuiopPD: revision 2
2023-01-24 yuiopPD-r2: refine, finish, and generate production files
2023-01-29 yuiopPD/r2: add dimension lines
2023-01-29 yuiopPD: plot dimensions
2023-06-02 gasket topplate for YUIOP60HH
2023-09-30 RP2040 based circuit schmatic
2023-09-30 add YUIOP/PM2 (WIP)
2023-09-30 add YUIOP32DM/lefty (wip)
2024-03-29 combined multiple symbol files for RP2040 into one
2024-03-29 yuiop2040C: RP2040 compact board
2024-03-29 YUIOP2040C: start plotting
2024-03-29 remove unnecessary file
2024-04-01 convert for KiCad 8
2024-04-07 KiCad 8: convert yuiop2040C
2024-08-01 convert topplate to KiCad 8.0
2024-08-01 add: yuiop60hh/main
2024-08-01 convert some projects to KiCad 8.0
2024-08-01 update sub-projects
2024-08-01 convert yuiop2040C project to KiCad 8.0
2024-08-03 convert yuiop2040 for KiCad 8
2024-08-03 split RP2040 core
2024-09-14 import symbols and footprints from Switch Science
2024-09-14 yuiop29re: start a new project
2024-09-14 update foostan/kbd
2024-09-14 yuiop29re: improve TRRS jack
2024-09-15 update TRRS jack footprint to new version
2024-09-15 fix OLED footprint
2024-09-15 yuiop29re: wiring completed
2024-09-16 yuiop29re: finished top plate
2024-09-16 yuiop29re: add JLC serial position mark
2024-09-16 yiuop29re: add product marks
2024-09-16 yuiop29re: plot gerbers
2024-09-17 yuiop29re: BOM
2024-10-04 yuiop29re: case panel
2024-10-15 revise yuiop29re
2026-01-31 parts check sheet
